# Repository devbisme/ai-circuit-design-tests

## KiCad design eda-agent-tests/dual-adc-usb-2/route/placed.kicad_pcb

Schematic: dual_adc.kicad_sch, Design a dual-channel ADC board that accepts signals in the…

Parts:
C1, C11, C18, C25: 4.7uF
C2, C4, C6, C7, C10, C49, C50, C54, C55: 1uF
C3, C5, C8, C61, C69, C80, C81, C83, C93: 10uF
C9, C12, C13, C48, C51, C53, C56: 2.2uF
C14: 4.7nF
C15, C19, C20, C21, C22, C23, C24, C26, C27, C28, C29, C30, C36, C37, C44, C45, C47, C52, C57, C58, C59, C60, C62, C63, C64, C65, C66, C67, C68, C70, C71, C72, C73, C74, C75, C76, C77, C78, C79, C82, C84, C85, C86, C87, C88, C89, C90, C91, C92: 100nF
C16, C17: 27pF
C31, C39: 12pF
C32, C40: 2.7pF
C33, C41: 22pF
C34, C35, C42, C43: 33pF
C38, C46: 100pF
D1: Green
D2, D3: BAV99
D4, D5: Yellow
F1: 750mA
FB1: 120R@100MHz 2A
FB2, FB3: 600R@100MHz
H1, H2, H3, H4: MountingHole
J1: USB_B
J2: BNC_A
J3: BNC_B
J4: PROG
R1, R9, R10, R12, R13, R14, R33, R40, R41, R42, R43, R44: 10k
R2: 232k
R3, R5: 100k
R4: 226k
R6, R17, R18, R19, R20, R21, R26, R27, R28, R29, R30, R45, R46: 1k
R7: 1M
R8: 12k
R11: 2.2k
R15, R24: 909k
R16, R25: 90.9k
R22, R23, R31, R32: 49.9
R34: 20k
R35, R36, R37: 33
R38, R39: 100
RN1, RN2, RN3, RN4, RN5, RN6, RN7: 33
U1: AP2112K-3.3
U2: AP2112K-1.2
U3: LP5907MFX-3.3
U4: LM27762
U5: USBLC6-2SC6
U6: FT232HL
U7: 93LC56B
U8: OPA1656ID
U9, U10: THS4521ID
U11: LTC2290CUP
U12: ICE40HX4K-TQ144
U13: W25Q32JVSS
U14: MT48LC16M16A2TG-6A
X1: ASE-10.000MHz
Y1: 12MHz

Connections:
+1V2: C5.1, C65.1, C66.1, C67.1, C68.1, C69.1, R38.1, R39.1; also elsewhere on the board
+3V3A: C7.1, C8.1, C36.1, C44.1, C57.1, C58.1, C59.1, C60.1, C61.1, FB3.1, R33.1; also elsewhere on the board
+4V: C12.1, C29.1, D2.2 (A), D3.2 (A), R2.1, U4.11 (OUT+); also elsewhere on the board
+5V: C1.1, C2.1, C6.1, C9.1, FB1.2, U4.3 (VIN), U4.8 (EN-), U4.12 (EN+); also elsewhere on the board
-4V: C13.1, C30.1, D2.1 (K), D3.1 (K), R4.1, U4.6 (OUT-); also elsewhere on the board
ADC_CLKA: R35.2; also elsewhere on the board
ADC_CLKB: R36.2; also elsewhere on the board
ADC_DA0: RN1.8 (R1.2); also elsewhere on the board
ADC_DA0_R: RN1.1 (R1.1); also elsewhere on the board
ADC_DA1: RN1.7 (R2.2); also elsewhere on the board
ADC_DA1_R: RN1.2 (R2.1); also elsewhere on the board
ADC_DA2: RN1.6 (R3.2); also elsewhere on the board
ADC_DA2_R: RN1.3 (R3.1); also elsewhere on the board
ADC_DA3: RN1.5 (R4.2); also elsewhere on the board
ADC_DA3_R: RN1.4 (R4.1); also elsewhere on the board
ADC_DA4: RN2.8 (R1.2); also elsewhere on the board
ADC_DA4_R: RN2.1 (R1.1); also elsewhere on the board
ADC_DA5: RN2.7 (R2.2); also elsewhere on the board
ADC_DA5_R: RN2.2 (R2.1); also elsewhere on the board
ADC_DA6: RN2.6 (R3.2); also elsewhere on the board
ADC_DA6_R: RN2.3 (R3.1); also elsewhere on the board
ADC_DA7: RN2.5 (R4.2); also elsewhere on the board
ADC_DA7_R: RN2.4 (R4.1); also elsewhere on the board
ADC_DA8: RN3.8 (R1.2); also elsewhere on the board
ADC_DA8_R: RN3.1 (R1.1); also elsewhere on the board
ADC_DA9: RN3.7 (R2.2); also elsewhere on the board
ADC_DA9_R: RN3.2 (R2.1); also elsewhere on the board
ADC_DA10: RN3.6 (R3.2); also elsewhere on the board
ADC_DA10_R: RN3.3 (R3.1); also elsewhere on the board
ADC_DA11: RN3.5 (R4.2); also elsewhere on the board
ADC_DA11_R: RN3.4 (R4.1); also elsewhere on the board
ADC_DB0: RN4.7 (R2.2); also elsewhere on the board
ADC_DB0_R: RN4.2 (R2.1); also elsewhere on the board
ADC_DB1: RN4.6 (R3.2); also elsewhere on the board
ADC_DB1_R: RN4.3 (R3.1); also elsewhere on the board
ADC_DB2: RN4.5 (R4.2); also elsewhere on the board
ADC_DB2_R: RN4.4 (R4.1); also elsewhere on the board
ADC_DB3: RN5.8 (R1.2); also elsewhere on the board
ADC_DB3_R: RN5.1 (R1.1); also elsewhere on the board
ADC_DB4: RN5.7 (R2.2); also elsewhere on the board
ADC_DB4_R: RN5.2 (R2.1); also elsewhere on the board
ADC_DB5: RN5.6 (R3.2); also elsewhere on the board
ADC_DB5_R: RN5.3 (R3.1); also elsewhere on the board
ADC_DB6: RN5.5 (R4.2); also elsewhere on the board
ADC_DB6_R: RN5.4 (R4.1); also elsewhere on the board
ADC_DB7: RN6.8 (R1.2); also elsewhere on the board
ADC_DB7_R: RN6.1 (R1.1); also elsewhere on the board
ADC_DB8: RN6.7 (R2.2); also elsewhere on the board
ADC_DB8_R: RN6.2 (R2.1); also elsewhere on the board
ADC_DB9: RN6.6 (R3.2); also elsewhere on the board
ADC_DB9_R: RN6.3 (R3.1); also elsewhere on the board
ADC_DB10: RN6.5 (R4.2); also elsewhere on the board
ADC_DB10_R: RN6.4 (R4.1); also elsewhere on the board
ADC_DB11: RN7.8 (R1.2); also elsewhere on the board
ADC_DB11_R: RN7.1 (R1.1); also elsewhere on the board
ADC_MODE: R33.2, R34.1; also elsewhere on the board
ADC_OFA: RN4.8 (R1.2); also elsewhere on the board
ADC_OFA_R: RN4.1 (R1.1); also elsewhere on the board
ADC_OFB: RN7.7 (R2.2); also elsewhere on the board
ADC_OFB_R: RN7.2 (R2.1); also elsewhere on the board
AINA_N: C38.2, R23.2; also elsewhere on the board
AINA_P: C38.1, R22.2; also elsewhere on the board
AINB_N: C46.2, R32.2; also elsewhere on the board
AINB_P: C46.1, R31.2; also elsewhere on the board
CDONE: J4.8, R40.2; also elsewhere on the board
CFG_SCK: J4.3, U13.6 (CLK); also elsewhere on the board
CFG_SI: J4.7, U13.2 (DO/IO_{1}); also elsewhere on the board
CFG_SO: J4.5, U13.5 (DI/IO_{0}); also elsewhere on the board
CFG_SS_N: J4.1, R42.2, U13.1 (~CS); also elsewhere on the board
CLK10: R35.1, R36.1, R37.1, X1.3 (OUT)
CRESET_N: J4.4, R41.2; also elsewhere on the board
FDAA_ON: C34.1, R19.1, R23.1; also elsewhere on the board
FDAA_OP: C35.1, R21.1, R22.1; also elsewhere on the board
FDAA_SN: C35.2, R20.2, R21.2; also elsewhere on the board
FDAA_SP: C34.2, R18.2, R19.2; also elsewhere on the board
FDAB_ON: C42.1, R28.1, R32.1; also elsewhere on the board
FDAB_OP: C43.1, R30.1, R31.1; also elsewhere on the board
FDAB_SN: C43.2, R29.2, R30.2; also elsewhere on the board
FDAB_SP: C42.2, R27.2, R28.2; also elsewhere on the board
FLASH_HOLD_N: R44.2, U13.7 (~HOLD/~RESET/IO_{3})
FLASH_WP_N: R43.2, U13.3 (~WP/IO_{2})
FPGA_CLK10: R37.2; also elsewhere on the board
FT_ACBUS8: U6.32 (ACBUS8); also elsewhere on the board
FT_ACBUS9: U6.33 (ACBUS9); also elsewhere on the board
FT_CLKOUT: U6.29 (ACBUS5); also elsewhere on the board
FT_D0: U6.13 (ADBUS0); also elsewhere on the board
FT_D1: U6.14 (ADBUS1); also elsewhere on the board
FT_D2: U6.15 (ADBUS2); also elsewhere on the board
FT_D3: U6.16 (ADBUS3); also elsewhere on the board
FT_D4: U6.17 (ADBUS4); also elsewhere on the board
FT_D5: U6.18 (ADBUS5); also elsewhere on the board
FT_D6: U6.19 (ADBUS6); also elsewhere on the board
FT_D7: U6.20 (ADBUS7); also elsewhere on the board
FT_EECLK: R13.2, U6.44 (EECLK); also elsewhere on the board
FT_EECS: R12.2, U6.45 (EECS); also elsewhere on the board
FT_EEDATA: R11.2, R14.2, U6.43 (EEDATA); also elsewhere on the board
FT_EEDO: R11.1; also elsewhere on the board
FT_OE_N: U6.30 (ACBUS6); also elsewhere on the board
FT_PWRSAV_N: R9.2, U6.31 (ACBUS7)
FT_RD_N: U6.26 (ACBUS2); also elsewhere on the board
FT_REF: R8.1, U6.5 (REF)
FT_RESET_N: R10.2, U6.34 (~RESET)
FT_RXF_N: U6.21 (ACBUS0); also elsewhere on the board
FT_SIWU_N: U6.28 (ACBUS4); also elsewhere on the board
FT_TXE_N: U6.25 (ACBUS1); also elsewhere on the board
FT_VCCA: C26.1, U6.37 (VCCA)
FT_VCORE: C27.1, U6.38 (VCCCORE)
FT_VPHY: C18.1, C19.1, C20.1, FB2.2, U6.3 (VPHY), U6.8 (VPLL)
FT_WR_N: U6.27 (ACBUS3); also elsewhere on the board
FT_XI: C16.1, U6.1 (XCSI), Y1.1
FT_XO: C17.1, U6.2 (XCSO), Y1.3
INA_BUF: R18.1; also elsewhere on the board
INA_CLAMP: D2.3 (K), R17.2; also elsewhere on the board
INA_DIV: C32.2, C33.1, R15.2, R16.1, R17.1
INA_RAW: C31.1, C32.1, J2.1 (In), R15.1
INB_BUF: R27.1; also elsewhere on the board
INB_CLAMP: D3.3 (K), R26.2; also elsewhere on the board
INB_DIV: C40.2, C41.1, R24.2, R25.1, R26.1
INB_RAW: C39.1, C40.1, J3.1 (In), R24.1
LED1_A: D4.2 (A), R45.2
LED1_N: D4.1 (K); also elsewhere on the board
LED2_A: D5.2 (A), R46.2
LED2_N: D5.1 (K); also elsewhere on the board
LED_PWR: D1.2 (A), R6.2
LM_CN: C10.2, U4.9 (C-)
LM_CP: C11.1, U4.5 (CP)
LM_CPF: C10.1, U4.10 (C+)
LM_FBN: R4.2, R5.1, U4.7 (FB-)
LM_FBP: R2.2, R3.1, U4.2 (FB+)
LM_PGOOD_N: R1.2, U4.1 (PGOOD); also elsewhere on the board
OSC_VDD: C64.1, FB3.2, X1.1 (EN), X1.4 (Vdd)
REFHA: C47.1, C48.1, C49.1; also elsewhere on the board
REFHB: C52.1, C53.1, C54.1; also elsewhere on the board
REFLA: C47.2, C48.2, C50.1; also elsewhere on the board
REFLB: C52.2, C53.2, C55.1; also elsewhere on the board
SD_A0: U14.23 (A0); also elsewhere on the board
SD_A1: U14.24 (A1); also elsewhere on the board
SD_A2: U14.25 (A2); also elsewhere on the board
SD_A3: U14.26 (A3); also elsewhere on the board
SD_A4: U14.29 (A4); also elsewhere on the board
SD_A5: U14.30 (A5); also elsewhere on the board
SD_A6: U14.31 (A6); also elsewhere on the board
SD_A7: U14.32 (A7); also elsewhere on the board
SD_A8: U14.33 (A8); also elsewhere on the board
SD_A9: U14.34 (A9); also elsewhere on the board
SD_A10: U14.22 (A10); also elsewhere on the board
SD_A11: U14.35 (A11); also elsewhere on the board
SD_A12: U14.36 (A12); also elsewhere on the board
SD_BA0: U14.20 (BA0); also elsewhere on the board
SD_BA1: U14.21 (BA1); also elsewhere on the board
SD_CAS_N: U14.17 (~CAS); also elsewhere on the board
SD_CKE: U14.37 (CKE); also elsewhere on the board
SD_CLK: U14.38 (CLK); also elsewhere on the board
SD_CS_N: U14.19 (~CS); also elsewhere on the board
SD_DQ0: U12.110 (IOT_168), U14.2 (DQ0)
SD_DQ1: U12.112 (IOT_169), U14.4 (DQ1)
SD_DQ2: U12.113 (IOT_170), U14.5 (DQ2)
SD_DQ3: U12.114 (IOT_171), U14.7 (DQ3)
SD_DQ4: U12.115 (IOT_172), U14.8 (DQ4)
SD_DQ5: U12.116 (IOT_173), U14.10 (DQ5)
SD_DQ6: U12.117 (IOT_174), U14.11 (DQ6)
SD_DQ7: U12.118 (IOT_177), U14.13 (DQ7)
SD_DQ8: U12.119 (IOT_178), U14.42 (DQ8)
SD_DQ9: U12.120 (IOT_179), U14.44 (DQ9)
SD_DQ10: U12.121 (IOT_181), U14.45 (DQ10)
SD_DQ11: U12.122 (IOT_190), U14.47 (DQ11)
SD_DQ12: U12.124 (IOT_191), U14.48 (DQ12)
SD_DQ13: U12.125 (IOT_192), U14.50 (DQ13)
SD_DQ14: U12.128 (IOT_197_GBIN1), U14.51 (DQ14)
SD_DQ15: U12.129 (IOT_198_GBIN0), U14.53 (DQ15)
SD_DQMH: U14.39 (DQMH); also elsewhere on the board
SD_DQML: U14.15 (DQML); also elsewhere on the board
SD_RAS_N: U14.18 (~RAS); also elsewhere on the board
SD_WE_N: U14.16 (~WE); also elsewhere on the board
USB_DM: J1.2 (D-), U6.6 (DM); also elsewhere on the board
USB_DP: J1.3 (D+), U6.7 (DP); also elsewhere on the board
USB_SHIELD: C14.1, R7.1; also elsewhere on the board
VBUS: F1.1, J1.1 (VBUS)
VBUS_F: C15.1, F1.2, FB1.1; also elsewhere on the board
VCCPLL0: C81.1, C82.1, R38.2; also elsewhere on the board
VCCPLL1: C83.1, C84.1, R39.2; also elsewhere on the board
VCMA: C37.1, C51.1; also elsewhere on the board
VCMB: C45.1, C56.1; also elsewhere on the board

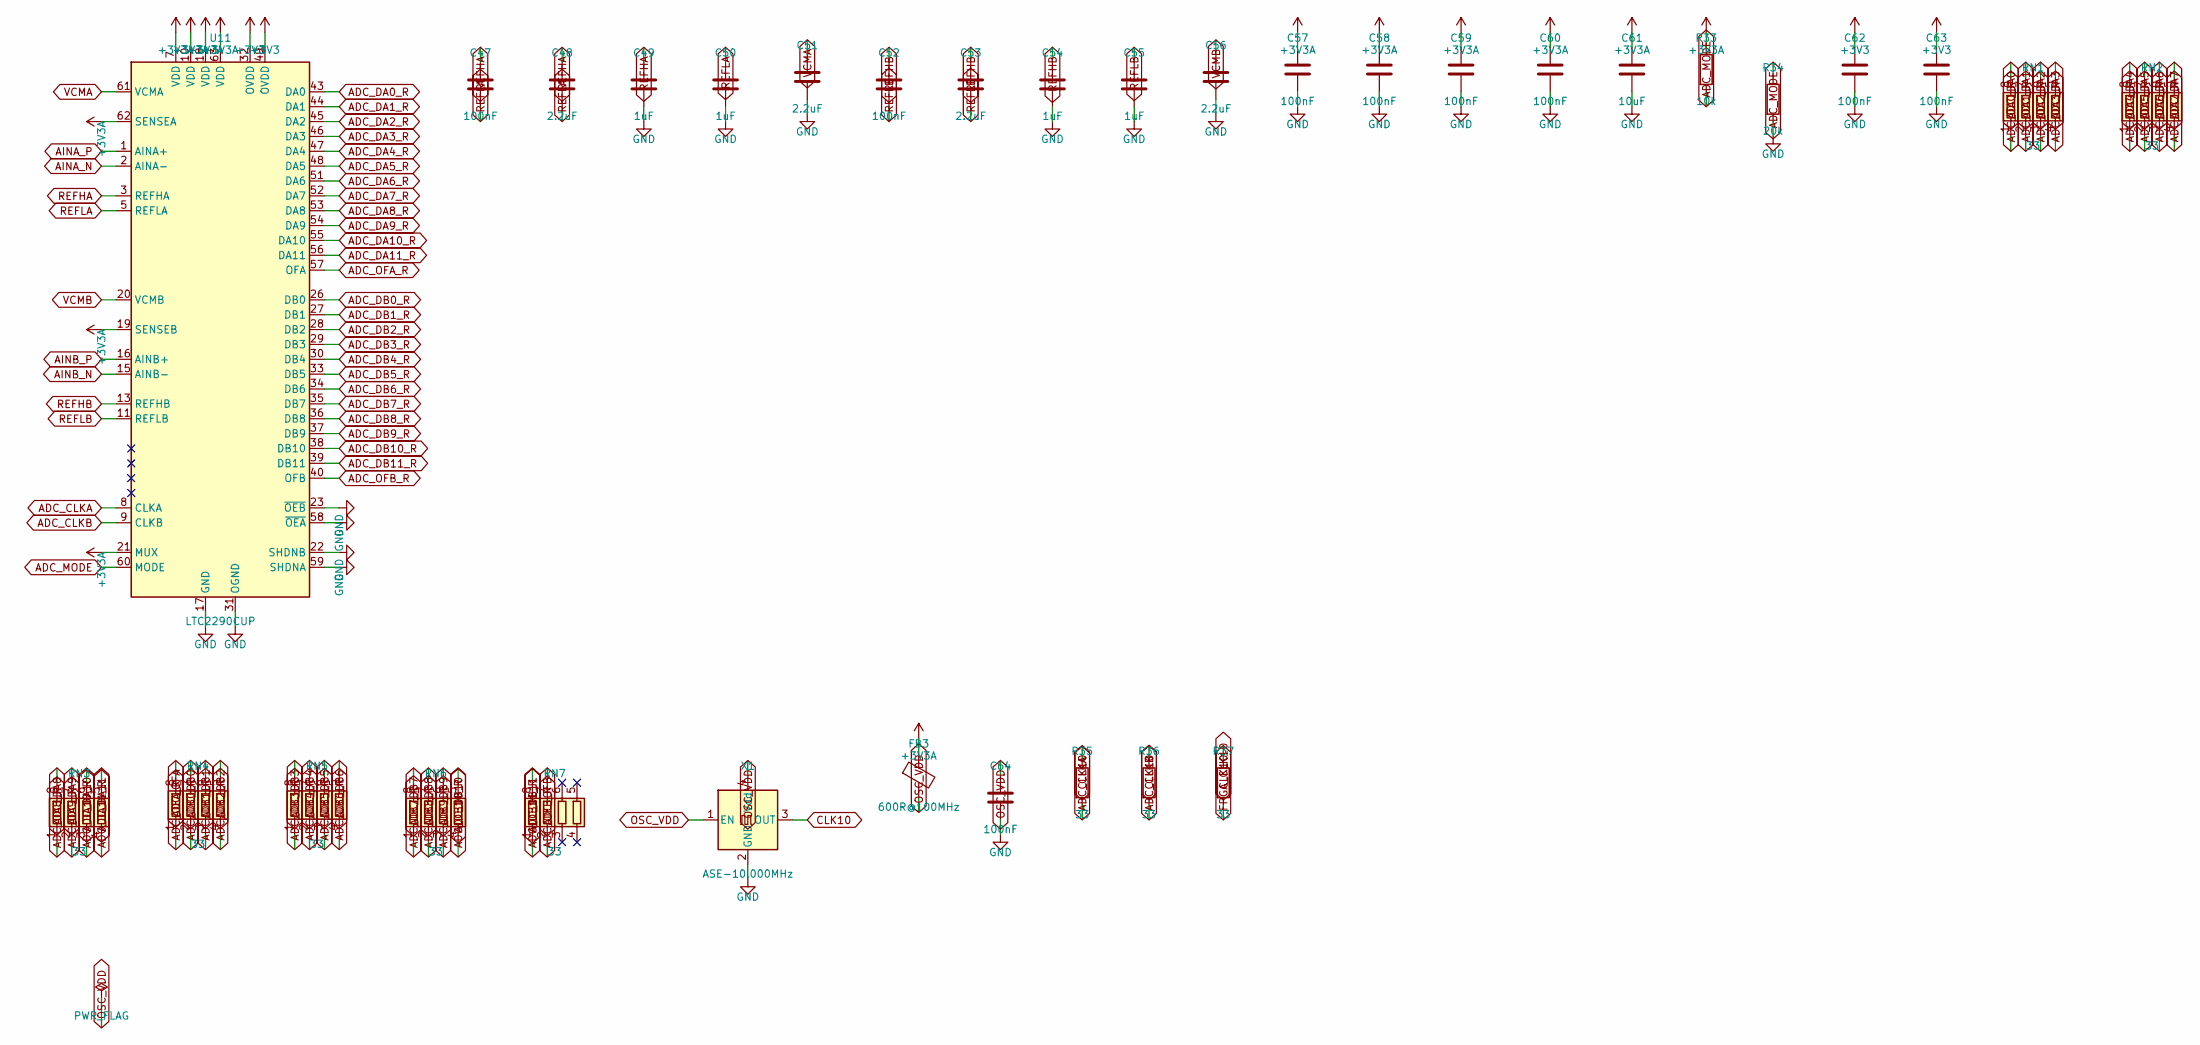
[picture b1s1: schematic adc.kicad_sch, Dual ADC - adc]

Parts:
C47, C52, C57, C58, C59, C60, C62, C63, C64: 100nF; C_0603_1608Metric
C48, C51, C53, C56: 2.2uF; C_0805_2012Metric
C49, C50, C54, C55: 1uF; C_0603_1608Metric
C61: 10uF; C_0805_2012Metric
FB3: 600R@100MHz; L_0603_1608Metric; MPN BLM18AG601SN1D
R33: 10k; R_0603_1608Metric
R34: 20k; R_0603_1608Metric
R35, R36, R37: 33; R_0603_1608Metric
RN1, RN2, RN3, RN4, RN5, RN6, RN7: 33; R_Array_Convex_4x0603; MPN CAY16-330J4LF
U11: LTC2290CUP; QFN-64-1EP_9x9mm_P0.5mm_EP7.15x7.15mm; MPN LTC2290CUP#PBF
X1: ASE-10.000MHz; Oscillator_SMD_Abracon_ASE-4Pin_3.2x2.5mm; MPN ASE-10.000MHZ-LC-T

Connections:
+3V3A: C57.1, C58.1, C59.1, C60.1, C61.1, FB3.1, R33.1, U11.7 (VDD), U11.10 (VDD), U11.18 (VDD), U11.19 (SENSEB), U11.21 (MUX), U11.62 (SENSEA), U11.63 (VDD); also elsewhere on the board
ADC_CLKA: R35.2, U11.8 (CLKA)
ADC_CLKB: R36.2, U11.9 (CLKB)
ADC_DA0: RN1.8 (R1.2); also elsewhere on the board
ADC_DA0_R: RN1.1 (R1.1), U11.43 (DA0)
ADC_DA1: RN1.7 (R2.2); also elsewhere on the board
ADC_DA1_R: RN1.2 (R2.1), U11.44 (DA1)
ADC_DA2: RN1.6 (R3.2); also elsewhere on the board
ADC_DA2_R: RN1.3 (R3.1), U11.45 (DA2)
ADC_DA3: RN1.5 (R4.2); also elsewhere on the board
ADC_DA3_R: RN1.4 (R4.1), U11.46 (DA3)
ADC_DA4: RN2.8 (R1.2); also elsewhere on the board
ADC_DA4_R: RN2.1 (R1.1), U11.47 (DA4)
ADC_DA5: RN2.7 (R2.2); also elsewhere on the board
ADC_DA5_R: RN2.2 (R2.1), U11.48 (DA5)
ADC_DA6: RN2.6 (R3.2); also elsewhere on the board
ADC_DA6_R: RN2.3 (R3.1), U11.51 (DA6)
ADC_DA7: RN2.5 (R4.2); also elsewhere on the board
ADC_DA7_R: RN2.4 (R4.1), U11.52 (DA7)
ADC_DA8: RN3.8 (R1.2); also elsewhere on the board
ADC_DA8_R: RN3.1 (R1.1), U11.53 (DA8)
ADC_DA9: RN3.7 (R2.2); also elsewhere on the board
ADC_DA9_R: RN3.2 (R2.1), U11.54 (DA9)
ADC_DA10: RN3.6 (R3.2); also elsewhere on the board
ADC_DA10_R: RN3.3 (R3.1), U11.55 (DA10)
ADC_DA11: RN3.5 (R4.2); also elsewhere on the board
ADC_DA11_R: RN3.4 (R4.1), U11.56 (DA11)
ADC_DB0: RN4.7 (R2.2); also elsewhere on the board
ADC_DB0_R: RN4.2 (R2.1), U11.26 (DB0)
ADC_DB1: RN4.6 (R3.2); also elsewhere on the board
ADC_DB1_R: RN4.3 (R3.1), U11.27 (DB1)
ADC_DB2: RN4.5 (R4.2); also elsewhere on the board
ADC_DB2_R: RN4.4 (R4.1), U11.28 (DB2)
ADC_DB3: RN5.8 (R1.2); also elsewhere on the board
ADC_DB3_R: RN5.1 (R1.1), U11.29 (DB3)
ADC_DB4: RN5.7 (R2.2); also elsewhere on the board
ADC_DB4_R: RN5.2 (R2.1), U11.30 (DB4)
ADC_DB5: RN5.6 (R3.2); also elsewhere on the board
ADC_DB5_R: RN5.3 (R3.1), U11.33 (DB5)
ADC_DB6: RN5.5 (R4.2); also elsewhere on the board
ADC_DB6_R: RN5.4 (R4.1), U11.34 (DB6)
ADC_DB7: RN6.8 (R1.2); also elsewhere on the board
ADC_DB7_R: RN6.1 (R1.1), U11.35 (DB7)
ADC_DB8: RN6.7 (R2.2); also elsewhere on the board
ADC_DB8_R: RN6.2 (R2.1), U11.36 (DB8)
ADC_DB9: RN6.6 (R3.2); also elsewhere on the board
ADC_DB9_R: RN6.3 (R3.1), U11.37 (DB9)
ADC_DB10: RN6.5 (R4.2); also elsewhere on the board
ADC_DB10_R: RN6.4 (R4.1), U11.38 (DB10)
ADC_DB11: RN7.8 (R1.2); also elsewhere on the board
ADC_DB11_R: RN7.1 (R1.1), U11.39 (DB11)
ADC_MODE: R33.2, R34.1, U11.60 (MODE)
ADC_OFA: RN4.8 (R1.2); also elsewhere on the board
ADC_OFA_R: RN4.1 (R1.1), U11.57 (OFA)
ADC_OFB: RN7.7 (R2.2); also elsewhere on the board
ADC_OFB_R: RN7.2 (R2.1), U11.40 (OFB)
AINA_N: U11.2 (AINA-); also elsewhere on the board
AINA_P: U11.1 (AINA+); also elsewhere on the board
AINB_N: U11.15 (AINB-); also elsewhere on the board
AINB_P: U11.16 (AINB+); also elsewhere on the board
CLK10: R35.1, R36.1, R37.1, X1.3 (OUT)
FPGA_CLK10: R37.2; also elsewhere on the board
OSC_VDD: C64.1, FB3.2, X1.1 (EN), X1.4 (Vdd)
REFHA: C47.1, C48.1, C49.1, U11.3 (REFHA), U11.4 (REFHA)
REFHB: C52.1, C53.1, C54.1, U11.13 (REFHB), U11.14 (REFHB)
REFLA: C47.2, C48.2, C50.1, U11.5 (REFLA), U11.6 (REFLA)
REFLB: C52.2, C53.2, C55.1, U11.11 (REFLB), U11.12 (REFLB)
VCMA: C51.1, U11.61 (VCMA); also elsewhere on the board
VCMB: C56.1, U11.20 (VCMB); also elsewhere on the board

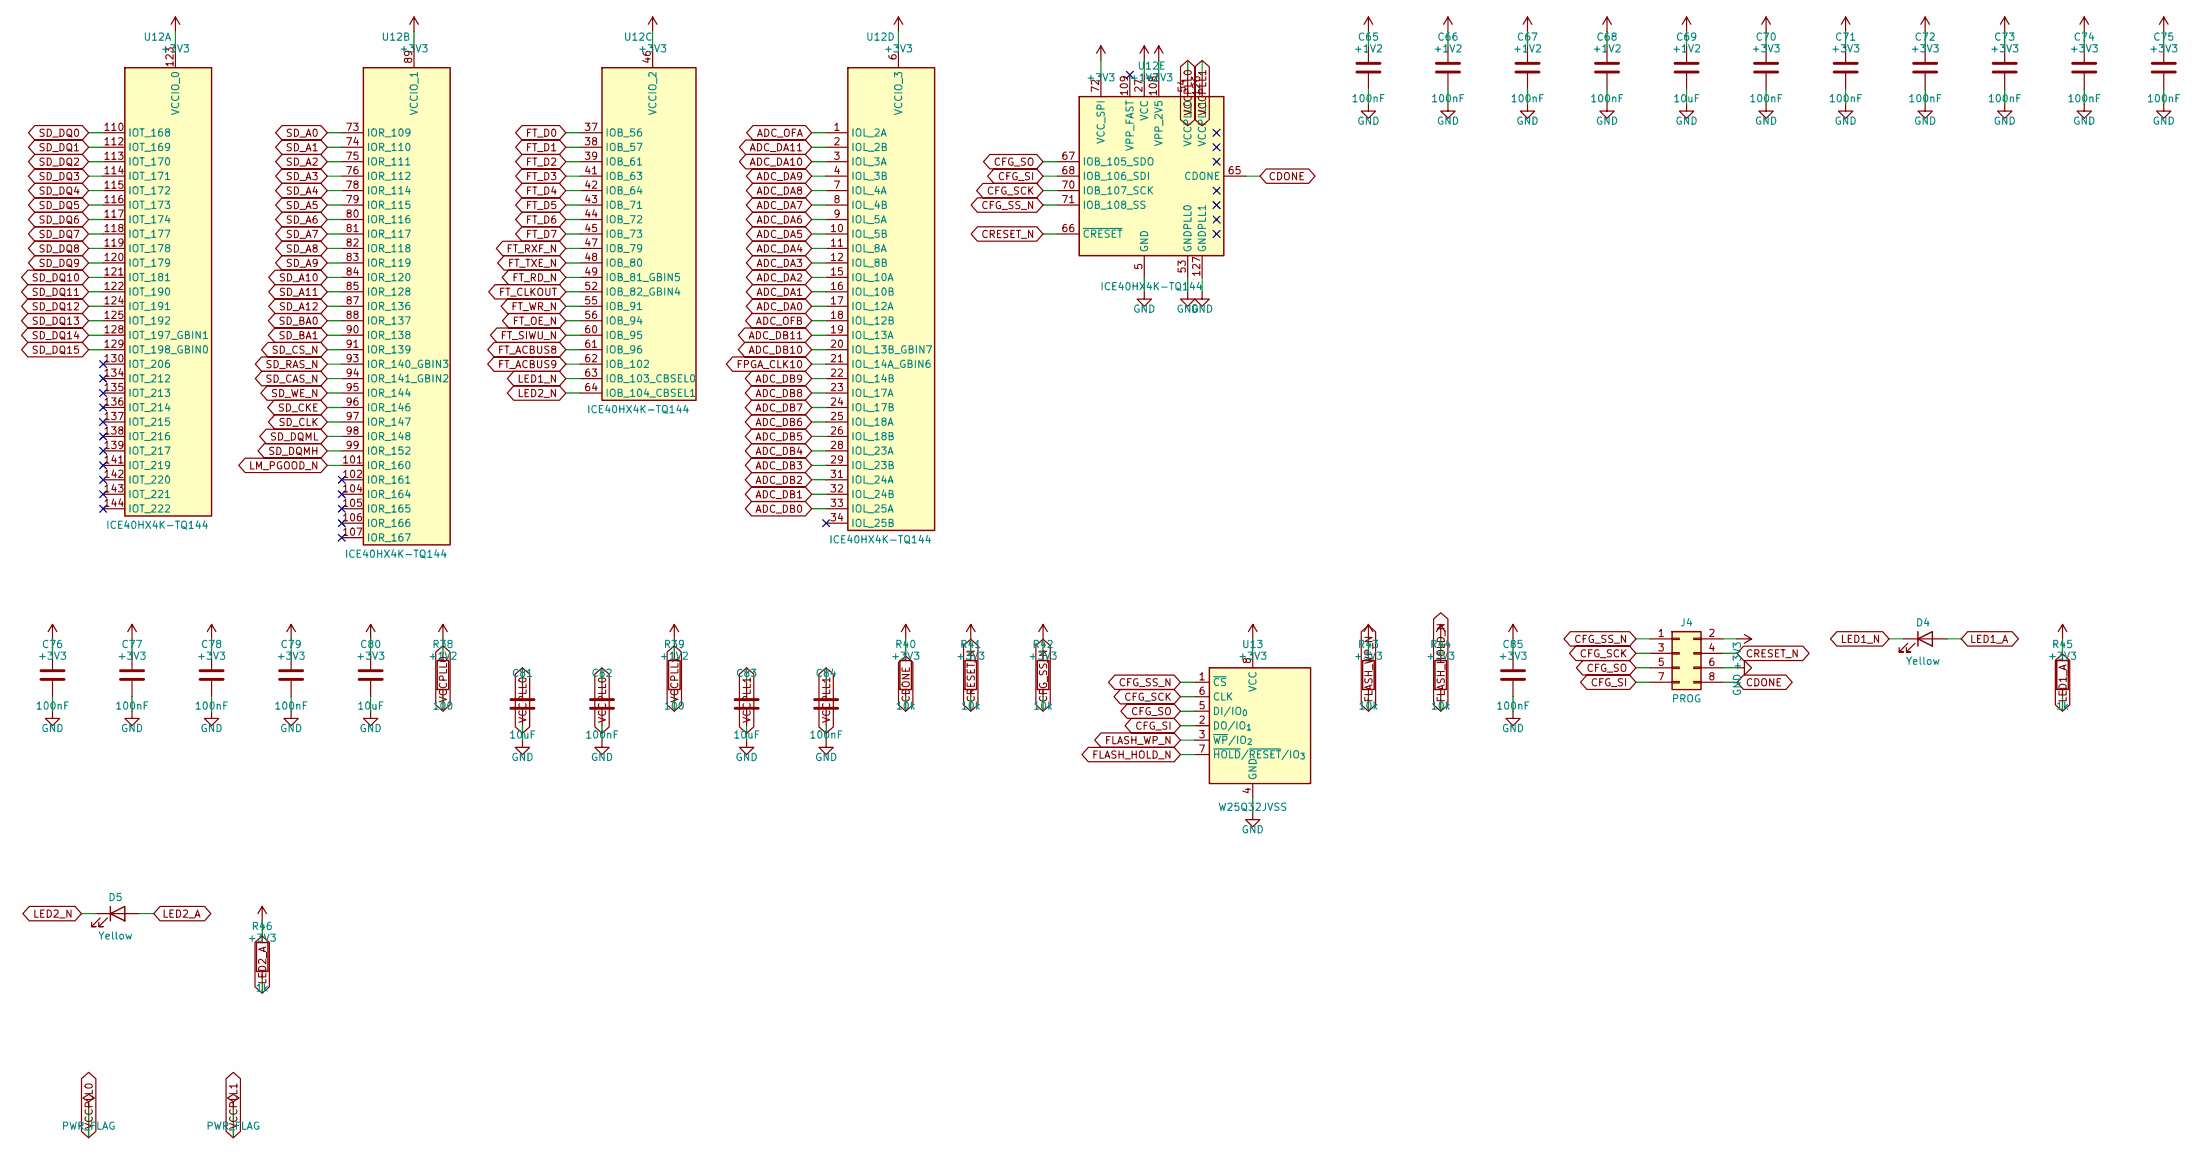
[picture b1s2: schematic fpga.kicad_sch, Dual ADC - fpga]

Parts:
C65, C66, C67, C68, C70, C71, C72, C73, C74, C75, C76, C77, C78, C79, C82, C84, C85: 100nF; C_0603_1608Metric
C69, C80, C81, C83: 10uF; C_0805_2012Metric
D4, D5: Yellow; LED_0603_1608Metric
J4: PROG; PinHeader_2x04_P2.54mm_Vertical
R38, R39: 100; R_0603_1608Metric
R40, R41, R42, R43, R44: 10k; R_0603_1608Metric
R45, R46: 1k; R_0603_1608Metric
U12: ICE40HX4K-TQ144; TQFP-144_20x20mm_P0.5mm; MPN ICE40HX4K-TQ144
U13: W25Q32JVSS; SOIC-8_5.3x5.3mm_P1.27mm; MPN W25Q32JVSSIQ

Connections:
+1V2: C65.1, C66.1, C67.1, C68.1, C69.1, R38.1, R39.1, U12.27 (VCC), U12.40 (VCC), U12.92 (VCC), U12.111 (VCC); also elsewhere on the board
ADC_DA0: U12.17 (IOL_12A); also elsewhere on the board
ADC_DA1: U12.16 (IOL_10B); also elsewhere on the board
ADC_DA2: U12.15 (IOL_10A); also elsewhere on the board
ADC_DA3: U12.12 (IOL_8B); also elsewhere on the board
ADC_DA4: U12.11 (IOL_8A); also elsewhere on the board
ADC_DA5: U12.10 (IOL_5B); also elsewhere on the board
ADC_DA6: U12.9 (IOL_5A); also elsewhere on the board
ADC_DA7: U12.8 (IOL_4B); also elsewhere on the board
ADC_DA8: U12.7 (IOL_4A); also elsewhere on the board
ADC_DA9: U12.4 (IOL_3B); also elsewhere on the board
ADC_DA10: U12.3 (IOL_3A); also elsewhere on the board
ADC_DA11: U12.2 (IOL_2B); also elsewhere on the board
ADC_DB0: U12.33 (IOL_25A); also elsewhere on the board
ADC_DB1: U12.32 (IOL_24B); also elsewhere on the board
ADC_DB2: U12.31 (IOL_24A); also elsewhere on the board
ADC_DB3: U12.29 (IOL_23B); also elsewhere on the board
ADC_DB4: U12.28 (IOL_23A); also elsewhere on the board
ADC_DB5: U12.26 (IOL_18B); also elsewhere on the board
ADC_DB6: U12.25 (IOL_18A); also elsewhere on the board
ADC_DB7: U12.24 (IOL_17B); also elsewhere on the board
ADC_DB8: U12.23 (IOL_17A); also elsewhere on the board
ADC_DB9: U12.22 (IOL_14B); also elsewhere on the board
ADC_DB10: U12.20 (IOL_13B_GBIN7); also elsewhere on the board
ADC_DB11: U12.19 (IOL_13A); also elsewhere on the board
ADC_OFA: U12.1 (IOL_2A); also elsewhere on the board
ADC_OFB: U12.18 (IOL_12B); also elsewhere on the board
CDONE: J4.8, R40.2, U12.65 (CDONE)
CFG_SCK: J4.3, U12.70 (IOB_107_SCK), U13.6 (CLK)
CFG_SI: J4.7, U12.68 (IOB_106_SDI), U13.2 (DO/IO_{1})
CFG_SO: J4.5, U12.67 (IOB_105_SDO), U13.5 (DI/IO_{0})
CFG_SS_N: J4.1, R42.2, U12.71 (IOB_108_SS), U13.1 (~CS)
CRESET_N: J4.4, R41.2, U12.66 (~CRESET)
FLASH_HOLD_N: R44.2, U13.7 (~HOLD/~RESET/IO_{3})
FLASH_WP_N: R43.2, U13.3 (~WP/IO_{2})
FPGA_CLK10: U12.21 (IOL_14A_GBIN6); also elsewhere on the board
FT_ACBUS8: U12.61 (IOB_96); also elsewhere on the board
FT_ACBUS9: U12.62 (IOB_102); also elsewhere on the board
FT_CLKOUT: U12.52 (IOB_82_GBIN4); also elsewhere on the board
FT_D0: U12.37 (IOB_56); also elsewhere on the board
FT_D1: U12.38 (IOB_57); also elsewhere on the board
FT_D2: U12.39 (IOB_61); also elsewhere on the board
FT_D3: U12.41 (IOB_63); also elsewhere on the board
FT_D4: U12.42 (IOB_64); also elsewhere on the board
FT_D5: U12.43 (IOB_71); also elsewhere on the board
FT_D6: U12.44 (IOB_72); also elsewhere on the board
FT_D7: U12.45 (IOB_73); also elsewhere on the board
FT_OE_N: U12.56 (IOB_94); also elsewhere on the board
FT_RD_N: U12.49 (IOB_81_GBIN5); also elsewhere on the board
FT_RXF_N: U12.47 (IOB_79); also elsewhere on the board
FT_SIWU_N: U12.60 (IOB_95); also elsewhere on the board
FT_TXE_N: U12.48 (IOB_80); also elsewhere on the board
FT_WR_N: U12.55 (IOB_91); also elsewhere on the board
LED1_A: D4.2 (A), R45.2
LED1_N: D4.1 (K), U12.63 (IOB_103_CBSEL0)
LED2_A: D5.2 (A), R46.2
LED2_N: D5.1 (K), U12.64 (IOB_104_CBSEL1)
LM_PGOOD_N: U12.101 (IOR_160); also elsewhere on the board
SD_A0: U12.73 (IOR_109); also elsewhere on the board
SD_A1: U12.74 (IOR_110); also elsewhere on the board
SD_A2: U12.75 (IOR_111); also elsewhere on the board
SD_A3: U12.76 (IOR_112); also elsewhere on the board
SD_A4: U12.78 (IOR_114); also elsewhere on the board
SD_A5: U12.79 (IOR_115); also elsewhere on the board
SD_A6: U12.80 (IOR_116); also elsewhere on the board
SD_A7: U12.81 (IOR_117); also elsewhere on the board
SD_A8: U12.82 (IOR_118); also elsewhere on the board
SD_A9: U12.83 (IOR_119); also elsewhere on the board
SD_A10: U12.84 (IOR_120); also elsewhere on the board
SD_A11: U12.85 (IOR_128); also elsewhere on the board
SD_A12: U12.87 (IOR_136); also elsewhere on the board
SD_BA0: U12.88 (IOR_137); also elsewhere on the board
SD_BA1: U12.90 (IOR_138); also elsewhere on the board
SD_CAS_N: U12.94 (IOR_141_GBIN2); also elsewhere on the board
SD_CKE: U12.96 (IOR_146); also elsewhere on the board
SD_CLK: U12.97 (IOR_147); also elsewhere on the board
SD_CS_N: U12.91 (IOR_139); also elsewhere on the board
SD_DQ0: U12.110 (IOT_168); also elsewhere on the board
SD_DQ1: U12.112 (IOT_169); also elsewhere on the board
SD_DQ2: U12.113 (IOT_170); also elsewhere on the board
SD_DQ3: U12.114 (IOT_171); also elsewhere on the board
SD_DQ4: U12.115 (IOT_172); also elsewhere on the board
SD_DQ5: U12.116 (IOT_173); also elsewhere on the board
SD_DQ6: U12.117 (IOT_174); also elsewhere on the board
SD_DQ7: U12.118 (IOT_177); also elsewhere on the board
SD_DQ8: U12.119 (IOT_178); also elsewhere on the board
SD_DQ9: U12.120 (IOT_179); also elsewhere on the board
SD_DQ10: U12.121 (IOT_181); also elsewhere on the board
SD_DQ11: U12.122 (IOT_190); also elsewhere on the board
SD_DQ12: U12.124 (IOT_191); also elsewhere on the board
SD_DQ13: U12.125 (IOT_192); also elsewhere on the board
SD_DQ14: U12.128 (IOT_197_GBIN1); also elsewhere on the board
SD_DQ15: U12.129 (IOT_198_GBIN0); also elsewhere on the board
SD_DQMH: U12.99 (IOR_152); also elsewhere on the board
SD_DQML: U12.98 (IOR_148); also elsewhere on the board
SD_RAS_N: U12.93 (IOR_140_GBIN3); also elsewhere on the board
SD_WE_N: U12.95 (IOR_144); also elsewhere on the board
VCCPLL0: C81.1, C82.1, R38.2, U12.54 (VCCPLL0)
VCCPLL1: C83.1, C84.1, R39.2, U12.126 (VCCPLL1)

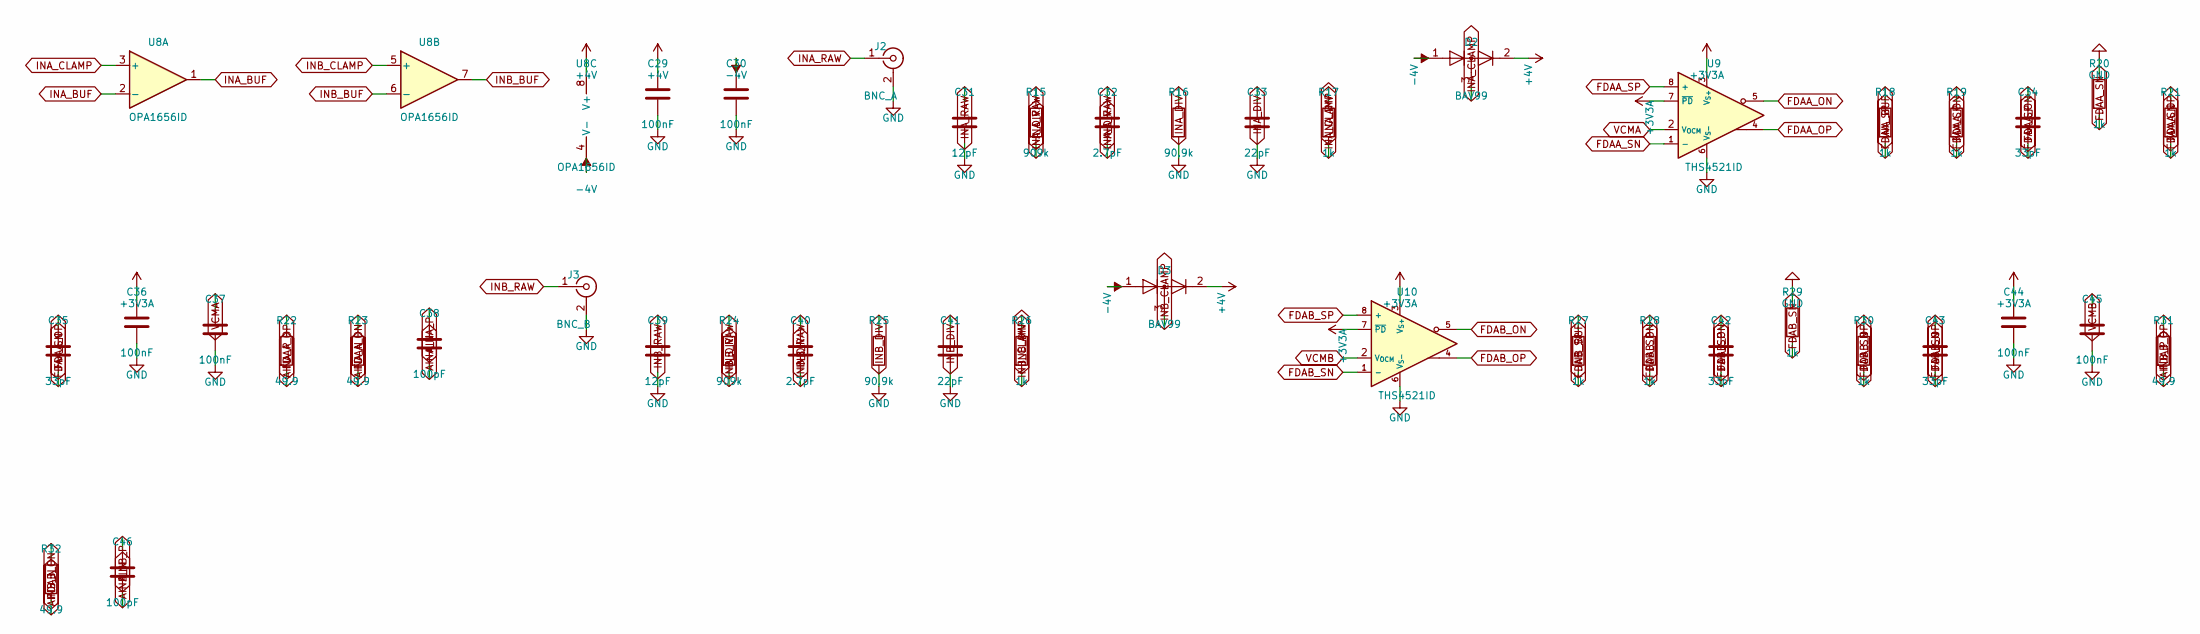
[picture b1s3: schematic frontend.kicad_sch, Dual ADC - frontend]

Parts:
C29, C30, C36, C37, C44, C45: 100nF; C_0603_1608Metric
C31, C39: 12pF; C_0603_1608Metric
C32, C40: 2.7pF; C_0603_1608Metric
C33, C41: 22pF; C_0603_1608Metric
C34, C35, C42, C43: 33pF; C_0603_1608Metric
C38, C46: 100pF; C_0603_1608Metric
D2, D3: BAV99; SOT-23; MPN BAV99,215
J2: BNC_A; BNC_Amphenol_B6252HB-NPP3G-50_Horizontal; MPN B6252HB-NPP3G-50
J3: BNC_B; BNC_Amphenol_B6252HB-NPP3G-50_Horizontal; MPN B6252HB-NPP3G-50
R15, R24: 909k; R_0603_1608Metric; Tolerance 0.1%
R16, R25: 90.9k; R_0603_1608Metric; Tolerance 0.1%
R17, R18, R19, R20, R21, R26, R27, R28, R29, R30: 1k; R_0603_1608Metric
R22, R23, R31, R32: 49.9; R_0603_1608Metric
U8: OPA1656ID; SOIC-8_3.9x4.9mm_P1.27mm; MPN OPA1656IDR
U9, U10: THS4521ID; SOIC-8_3.9x4.9mm_P1.27mm; MPN THS4521IDR

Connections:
+3V3A: C36.1, C44.1, U9.3 (V_{S+}), U9.7 (~PD), U10.3 (V_{S+}), U10.7 (~PD); also elsewhere on the board
+4V: C29.1, D2.2 (A), D3.2 (A), U8.8 (V+); also elsewhere on the board
-4V: C30.1, D2.1 (K), D3.1 (K), U8.4 (V-); also elsewhere on the board
AINA_N: C38.2, R23.2; also elsewhere on the board
AINA_P: C38.1, R22.2; also elsewhere on the board
AINB_N: C46.2, R32.2; also elsewhere on the board
AINB_P: C46.1, R31.2; also elsewhere on the board
FDAA_ON: C34.1, R19.1, R23.1, U9.5
FDAA_OP: C35.1, R21.1, R22.1, U9.4
FDAA_SN: C35.2, R20.2, R21.2, U9.1 (-)
FDAA_SP: C34.2, R18.2, R19.2, U9.8 (+)
FDAB_ON: C42.1, R28.1, R32.1, U10.5
FDAB_OP: C43.1, R30.1, R31.1, U10.4
FDAB_SN: C43.2, R29.2, R30.2, U10.1 (-)
FDAB_SP: C42.2, R27.2, R28.2, U10.8 (+)
INA_BUF: R18.1, U8.1, U8.2 (-)
INA_CLAMP: D2.3 (K), R17.2, U8.3 (+)
INA_DIV: C32.2, C33.1, R15.2, R16.1, R17.1
INA_RAW: C31.1, C32.1, J2.1 (In), R15.1
INB_BUF: R27.1, U8.6 (-), U8.7
INB_CLAMP: D3.3 (K), R26.2, U8.5 (+)
INB_DIV: C40.2, C41.1, R24.2, R25.1, R26.1
INB_RAW: C39.1, C40.1, J3.1 (In), R24.1
VCMA: C37.1, U9.2 (V_{OCM}); also elsewhere on the board
VCMB: C45.1, U10.2 (V_{OCM}); also elsewhere on the board

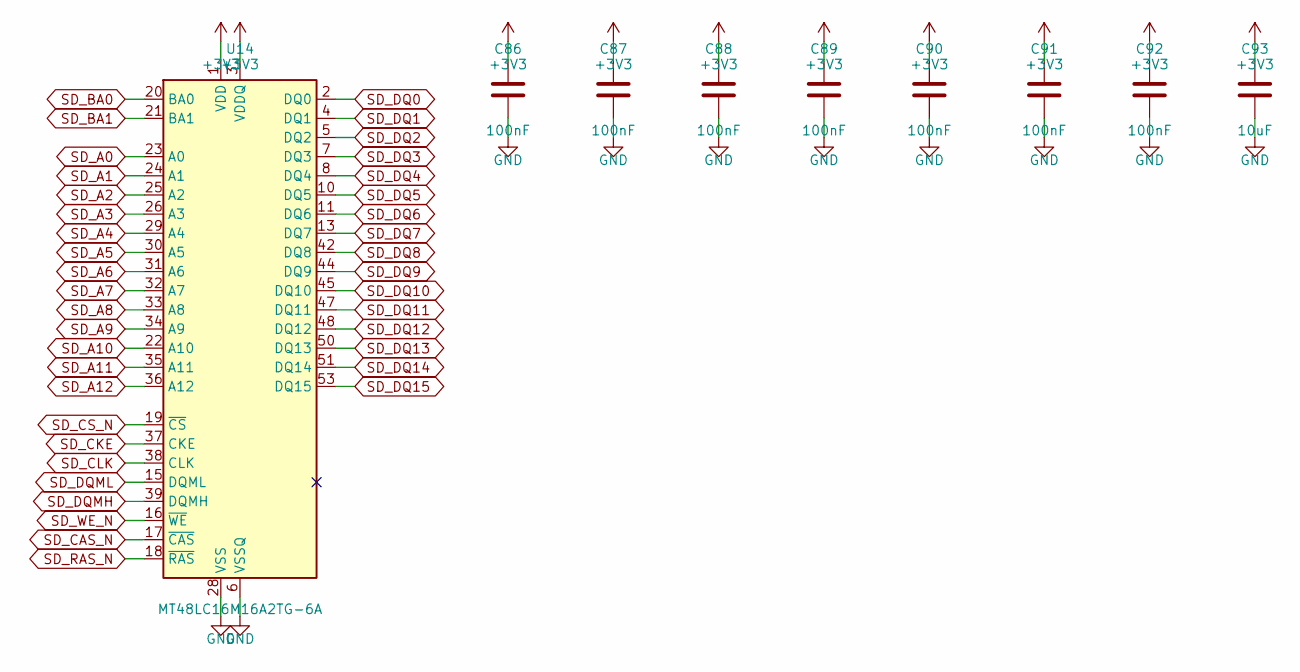
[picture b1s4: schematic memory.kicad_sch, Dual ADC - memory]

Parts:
C86, C87, C88, C89, C90, C91, C92: 100nF; C_0603_1608Metric
C93: 10uF; C_0805_2012Metric
U14: MT48LC16M16A2TG-6A; TSOP-II-54_22.2x10.16mm_P0.8mm; MPN MT48LC16M16A2P-6A:G

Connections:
SD_A0: U14.23 (A0); also elsewhere on the board
SD_A1: U14.24 (A1); also elsewhere on the board
SD_A2: U14.25 (A2); also elsewhere on the board
SD_A3: U14.26 (A3); also elsewhere on the board
SD_A4: U14.29 (A4); also elsewhere on the board
SD_A5: U14.30 (A5); also elsewhere on the board
SD_A6: U14.31 (A6); also elsewhere on the board
SD_A7: U14.32 (A7); also elsewhere on the board
SD_A8: U14.33 (A8); also elsewhere on the board
SD_A9: U14.34 (A9); also elsewhere on the board
SD_A10: U14.22 (A10); also elsewhere on the board
SD_A11: U14.35 (A11); also elsewhere on the board
SD_A12: U14.36 (A12); also elsewhere on the board
SD_BA0: U14.20 (BA0); also elsewhere on the board
SD_BA1: U14.21 (BA1); also elsewhere on the board
SD_CAS_N: U14.17 (~CAS); also elsewhere on the board
SD_CKE: U14.37 (CKE); also elsewhere on the board
SD_CLK: U14.38 (CLK); also elsewhere on the board
SD_CS_N: U14.19 (~CS); also elsewhere on the board
SD_DQ0: U14.2 (DQ0); also elsewhere on the board
SD_DQ1: U14.4 (DQ1); also elsewhere on the board
SD_DQ2: U14.5 (DQ2); also elsewhere on the board
SD_DQ3: U14.7 (DQ3); also elsewhere on the board
SD_DQ4: U14.8 (DQ4); also elsewhere on the board
SD_DQ5: U14.10 (DQ5); also elsewhere on the board
SD_DQ6: U14.11 (DQ6); also elsewhere on the board
SD_DQ7: U14.13 (DQ7); also elsewhere on the board
SD_DQ8: U14.42 (DQ8); also elsewhere on the board
SD_DQ9: U14.44 (DQ9); also elsewhere on the board
SD_DQ10: U14.45 (DQ10); also elsewhere on the board
SD_DQ11: U14.47 (DQ11); also elsewhere on the board
SD_DQ12: U14.48 (DQ12); also elsewhere on the board
SD_DQ13: U14.50 (DQ13); also elsewhere on the board
SD_DQ14: U14.51 (DQ14); also elsewhere on the board
SD_DQ15: U14.53 (DQ15); also elsewhere on the board
SD_DQMH: U14.39 (DQMH); also elsewhere on the board
SD_DQML: U14.15 (DQML); also elsewhere on the board
SD_RAS_N: U14.18 (~RAS); also elsewhere on the board
SD_WE_N: U14.16 (~WE); also elsewhere on the board
